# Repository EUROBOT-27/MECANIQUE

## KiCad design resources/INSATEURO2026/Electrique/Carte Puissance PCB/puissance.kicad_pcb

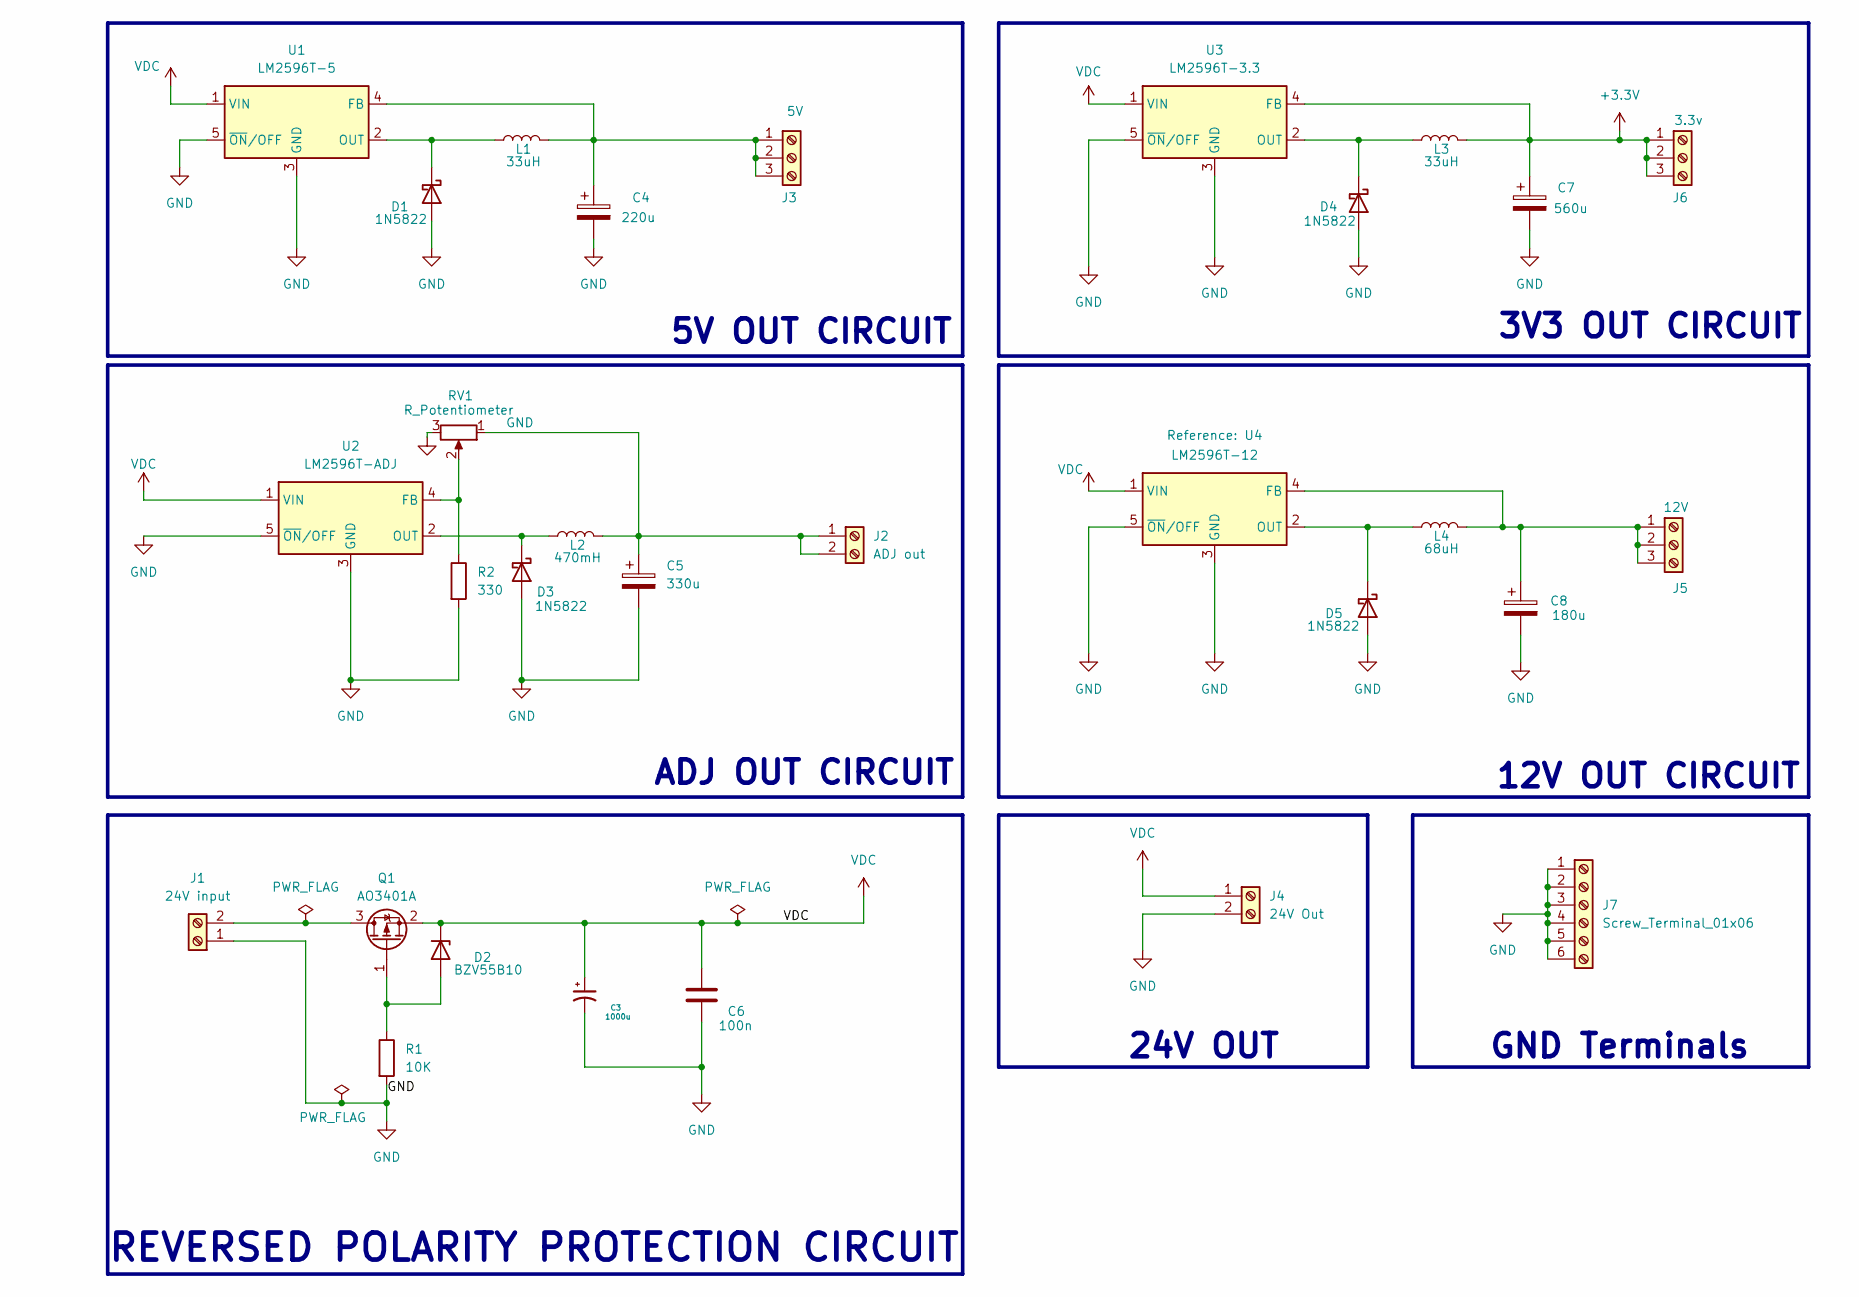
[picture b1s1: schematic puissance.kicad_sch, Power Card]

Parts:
C3: 1000u; CP_Elec_10x10.5
C4: 220u; CP_Elec_10x10.5
C5: 330u; CP_Elec_10x10.5
C6: 100n; C_1206_3216Metric_Pad1.33x1.80mm_HandSolder
C7: 560u; CP_Elec_10x10.5
C8: 180u; CP_Elec_10x10.5
D1, D3, D4, D5: 1N5822; D_DO-34_SOD68_P5.08mm_Vertical_AnodeUp
D2: BZV55B10; D_MiniMELF
J1: 24V input; Altech_AK100_1x02_P5.00mm
J2: ADJ out; Altech_AK100_1x02_P5.00mm
J3: 5V; Altech_AK100_1x03_P5.00mm
J4: 24V Out; Altech_AK100_1x02_P5.00mm
J5: 12V; Altech_AK100_1x03_P5.00mm
J6: 3.3v; Altech_AK100_1x03_P5.00mm
J7: Screw_Terminal_01x06; Altech_AK100_1x06_P5.00mm
L1, L3: 33uH; L_12x12mm_H6mm
L2: 470mH; L_12x12mm_H6mm
L4: 68uH; L_12x12mm_H6mm
Q1: AO3401A; SOT-23W
R1: 10K; R_1206_3216Metric_Pad1.30x1.75mm_HandSolder
R2: 330; R_1206_3216Metric_Pad1.30x1.75mm_HandSolder
RV1: R_Potentiometer; Potentiometer_Bourns_3296W_Vertical
U1: LM2596T-5; TO-263-5_TabPin3
U2: LM2596T-ADJ; TO-263-5_TabPin3
U3: LM2596T-3.3; TO-263-5_TabPin3
U4: LM2596T-12; TO-263-5_TabPin3

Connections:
+3.3V: C7.1, J6.1, J6.2, J6.3, L3.2, U3.4 (FB)
GND: C3.2, C4.2, C5.2, C6.2, C7.2, C8.2, D1.2 (A), D3.2 (A), D4.2 (A), D5.2 (A), J1.1, J4.2, J7.1, J7.2, J7.3, J7.4, J7.5, J7.6, R1.2, R2.2, RV1.3, U1.3 (GND), U1.5 (~ON/OFF), U2.3 (GND), U2.5 (~ON/OFF), U3.3 (GND), U3.5 (~ON/OFF), U4.3 (GND), U4.5 (~ON/OFF)
unnamed: D1.1 (K), L1.1, U1.2 (OUT)
unnamed: D2.2 (A), Q1.1 (G), R1.1
unnamed: D3.1 (K), L2.1, U2.2 (OUT)
unnamed: D4.1 (K), L3.1, U3.2 (OUT)
unnamed: D5.1 (K), L4.1, U4.2 (OUT)
unnamed: J1.2, Q1.3 (D)
unnamed: C5.1, J2.1, J2.2, L2.2, RV1.1
unnamed: C4.1, J3.1, J3.2, J3.3, L1.2, U1.4 (FB)
unnamed: C8.1, J5.1, J5.2, J5.3, L4.2, U4.4 (FB)
unnamed: R2.1, RV1.2, U2.4 (FB)
VDC: C3.1, C6.1, D2.1 (K), J4.1, Q1.2 (S), U1.1 (VIN), U2.1 (VIN), U3.1 (VIN), U4.1 (VIN)

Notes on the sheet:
5V OUT CIRCUIT
ADJ OUT CIRCUIT
12V OUT CIRCUIT
3V3 OUT CIRCUIT
REVERSED POLARITY PROTECTION CIRCUIT
24V OUT
GND Terminals

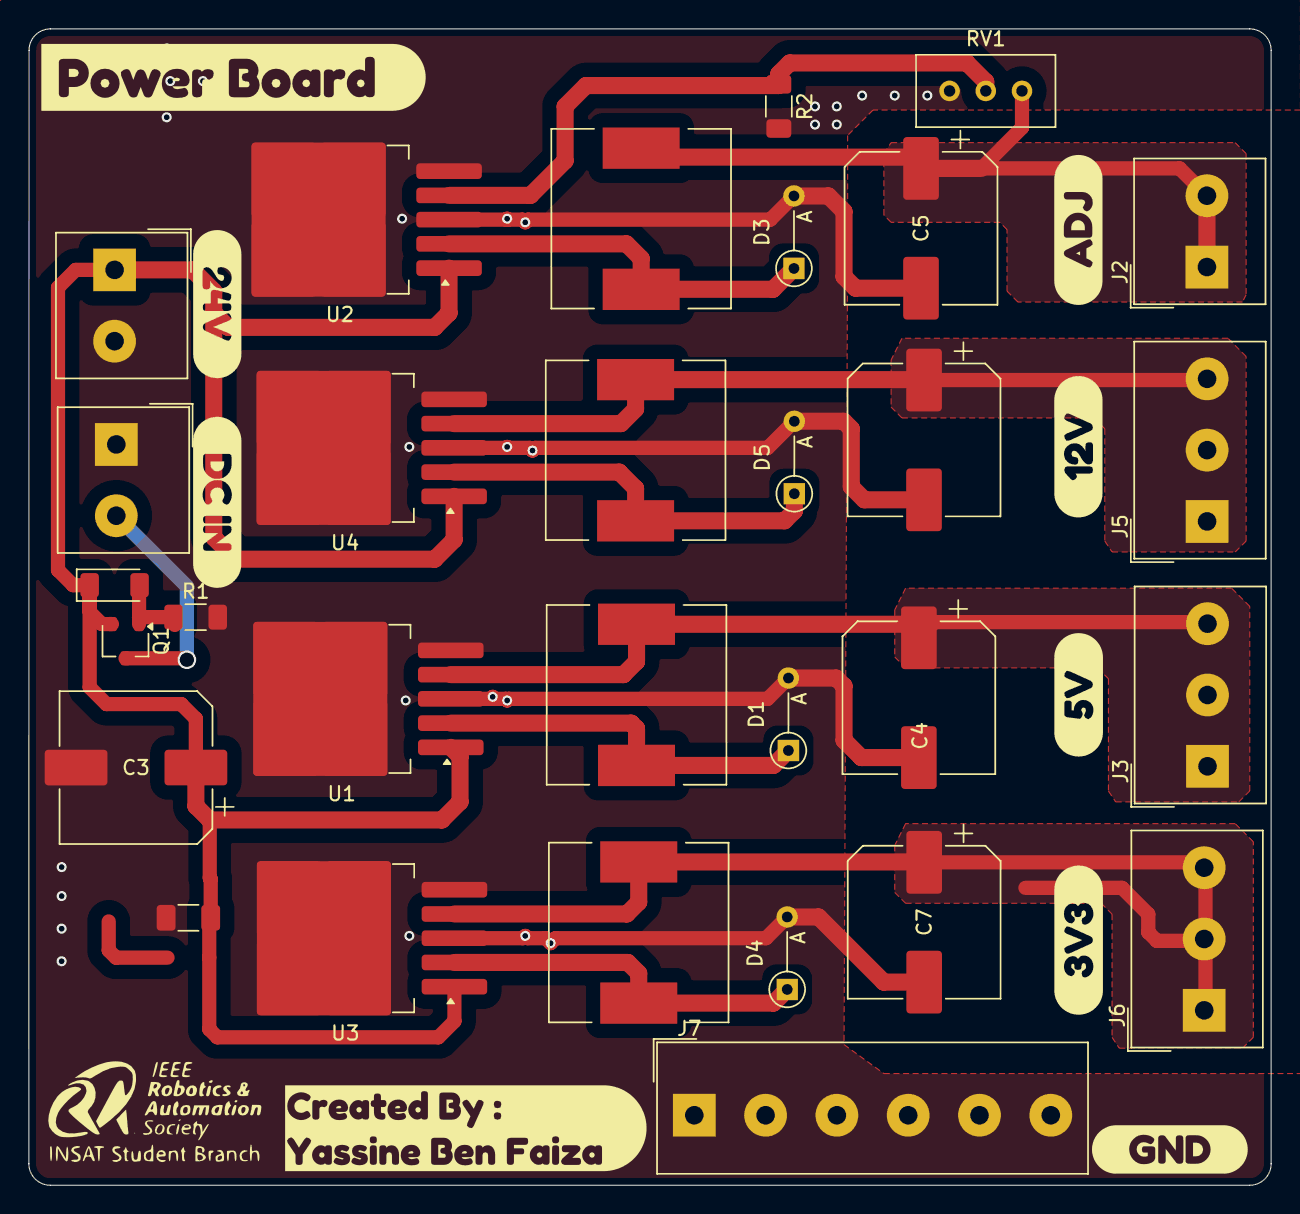
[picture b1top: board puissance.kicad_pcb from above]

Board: 2 copper layers, 87.1 x 81.1 mm, 39 parts (0 on the bottom side), 13 nets.

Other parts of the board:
kibuzzard-68827F3E: G***; kibuzzard-68827F3E
kibuzzard-679253A4: G***; kibuzzard-679253A4
kibuzzard-679255E3: G***; kibuzzard-679255E3
kibuzzard-688280F0: G***; kibuzzard-688280F0
kibuzzard-6792564A: G***; kibuzzard-6792564A
kibuzzard-67925436: G***; kibuzzard-67925436
kibuzzard-67925609: G***; kibuzzard-67925609
kibuzzard-67925625: G***; kibuzzard-67925625
kibuzzard-67925638: G***; kibuzzard-67925638

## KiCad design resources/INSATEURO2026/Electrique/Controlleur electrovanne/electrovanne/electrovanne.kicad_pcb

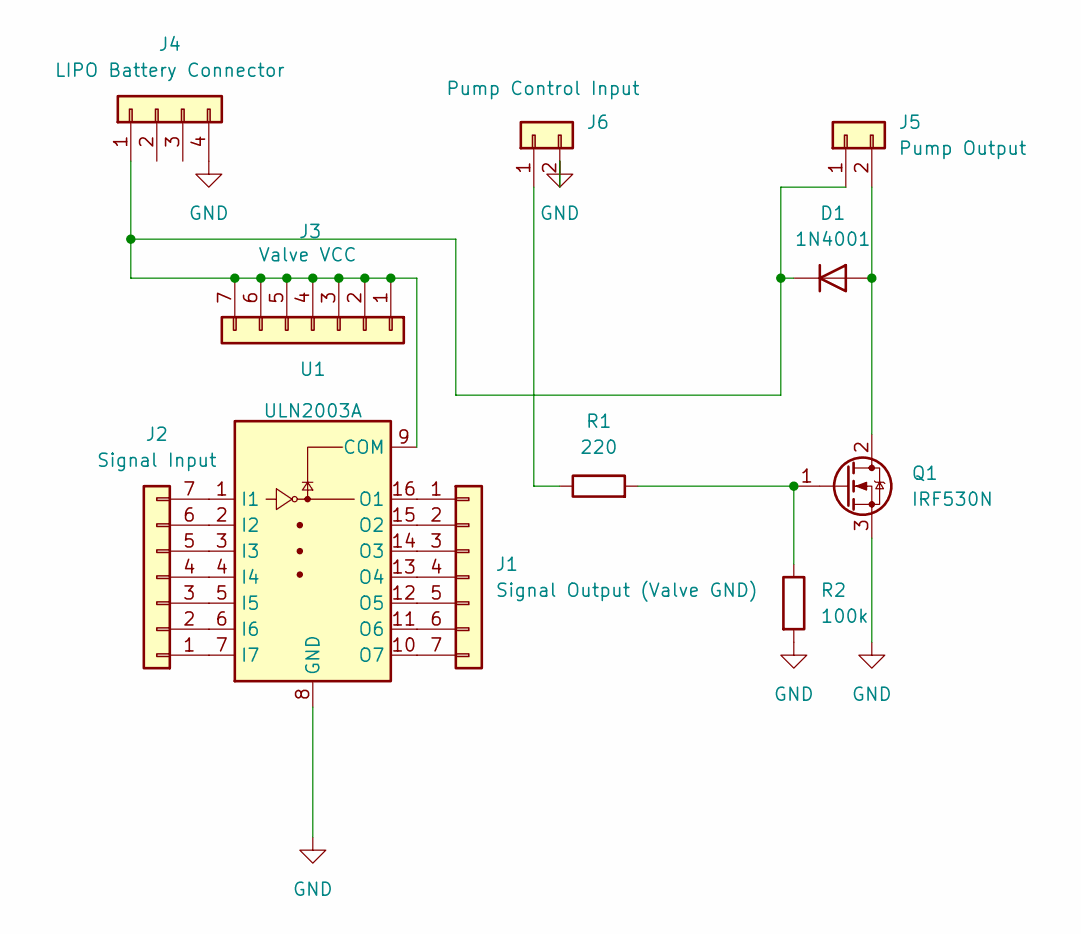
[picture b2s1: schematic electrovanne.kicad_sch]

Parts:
D1: 1N4001; D_DO-41_SOD81_P7.62mm_Horizontal
J1: Signal Output (Valve GND); PinSocket_1x08_P2.00mm_Vertical
J2: Signal Input; PinSocket_1x08_P2.00mm_Vertical
J3: Valve VCC; PinSocket_1x08_P2.00mm_Vertical
J4: LIPO Battery Connector; JST_XH_B4B-XH-A_1x04_P2.50mm_Vertical
J5: Pump Output; JST_EH_B2B-EH-A_1x02_P2.50mm_Vertical
J6: Pump Control Input; PinHeader_1x02_P1.00mm_Vertical
Q1: IRF530N; TO-220-3_Vertical
R1: 220; R_Axial_DIN0207_L6.3mm_D2.5mm_P15.24mm_Horizontal
R2: 100k; R_Axial_DIN0207_L6.3mm_D2.5mm_P15.24mm_Horizontal
U1: ULN2003A; DIP-16_W7.62mm

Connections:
GND: J4.4, J6.2, Q1.3 (S), R2.2, U1.8 (GND)
unnamed: D1.2 (A), J5.2, Q1.2 (D)
unnamed: D1.1 (K), J3.1, J3.2, J3.3, J3.4, J3.5, J3.6, J3.7, J4.1, J5.1, U1.9 (COM)
unnamed: J1.1, U1.16 (O1)
unnamed: J1.2, U1.15 (O2)
unnamed: J1.3, U1.14 (O3)
unnamed: J1.4, U1.13 (O4)
unnamed: J1.5, U1.12 (O5)
unnamed: J1.6, U1.11 (O6)
unnamed: J1.7, U1.10 (O7)
unnamed: J2.1, U1.7 (I7)
unnamed: J2.2, U1.6 (I6)
unnamed: J2.3, U1.5 (I5)
unnamed: J2.4, U1.4 (I4)
unnamed: J2.5, U1.3 (I3)
unnamed: J2.6, U1.2 (I2)
unnamed: J2.7, U1.1 (I1)
unnamed: J6.1, R1.1
unnamed: Q1.1 (G), R1.2, R2.1

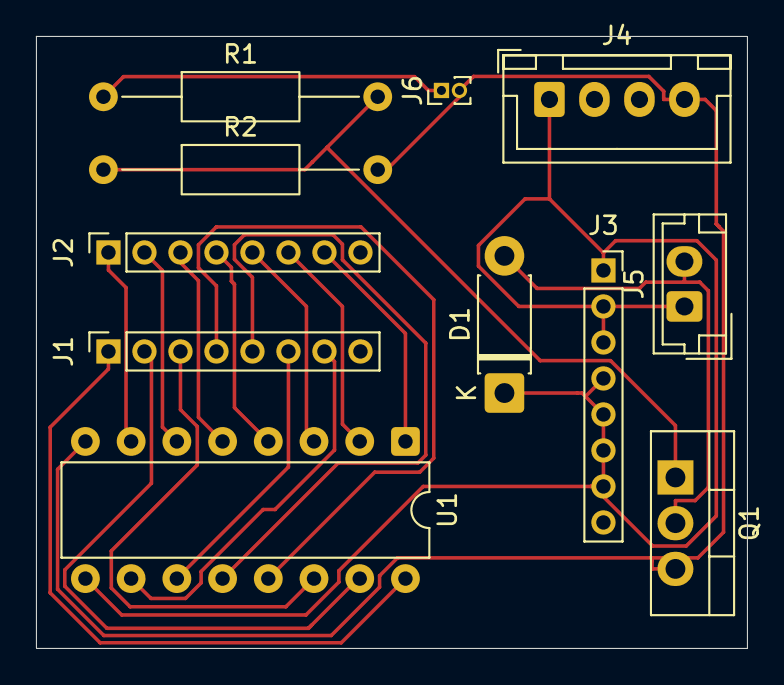
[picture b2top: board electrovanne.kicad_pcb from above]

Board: 2 copper layers, 39.5 x 34.0 mm, 11 parts (0 on the bottom side), 19 nets.

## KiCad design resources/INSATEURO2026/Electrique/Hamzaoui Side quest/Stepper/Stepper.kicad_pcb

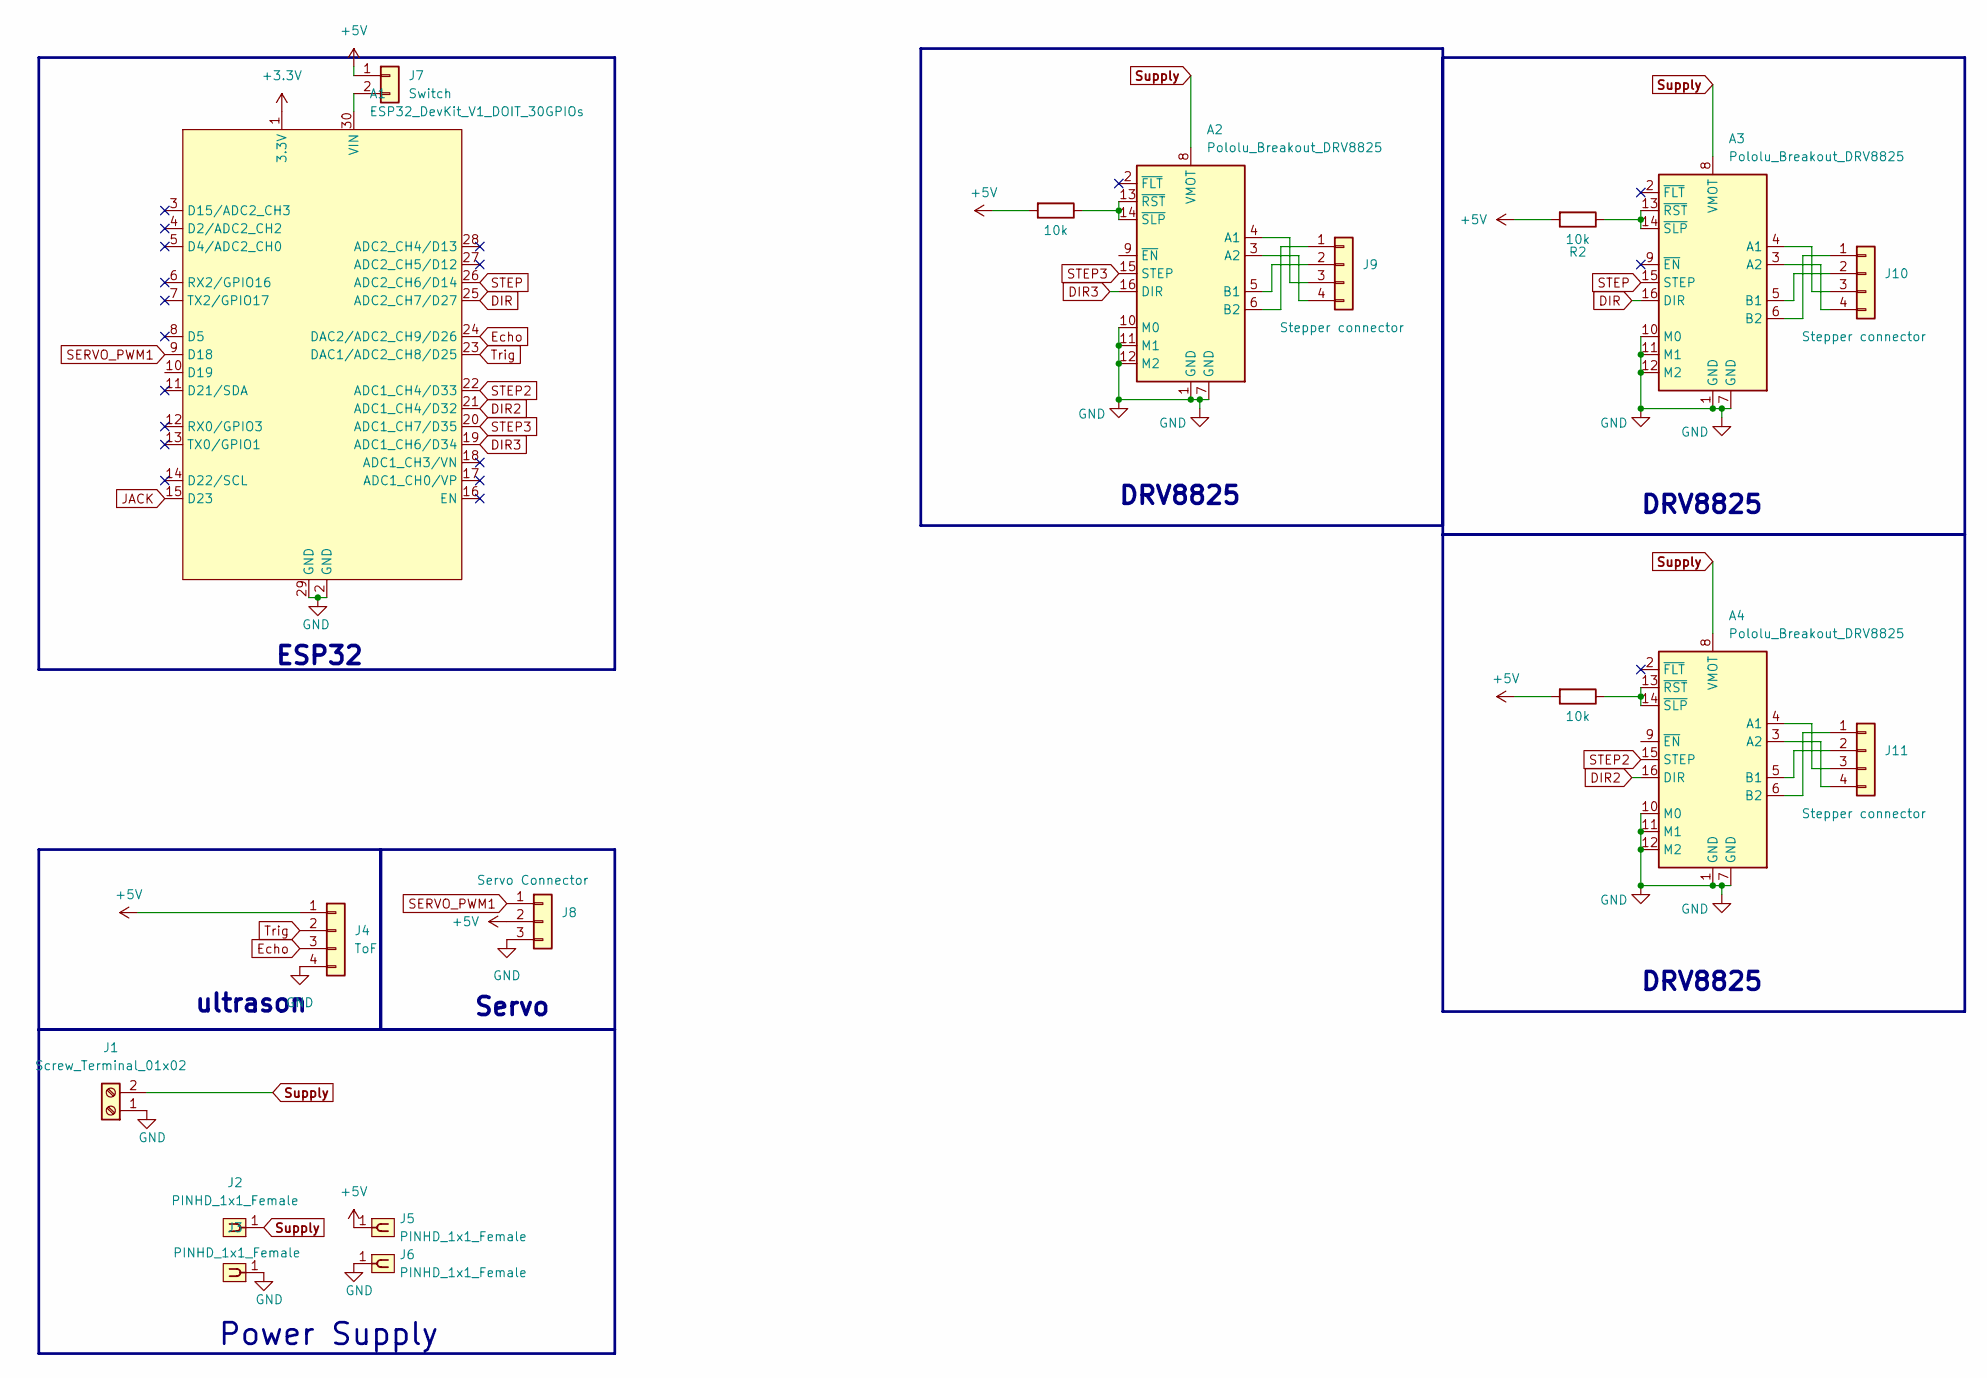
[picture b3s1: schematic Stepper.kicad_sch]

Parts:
A1: ESP32_DevKit_V1_DOIT_30GPIOs; DOIT_ESP32_DEVKIT_30Pins
A2, A3, A4: Pololu_Breakout_DRV8825; Pololu_Breakout-16_15.2x20.3mm
J1: Screw_Terminal_01x02; TerminalBlock_Altech_AK300-2_P5.00mm
J2, J3, J5, J6: PINHD_1x1_Female; PinSocket_1x01_P2.54mm_Vertical
J4: ToF; JST_EH_B4B-EH-A_1x04_P2.50mm_Vertical
J7: Switch; JST_PH_B2B-PH-K_1x02_P2.00mm_Vertical
J8: Servo Connector; PinHeader_1x03_P2.54mm_Vertical; Part Number 1-0301FBV0T
J9, J10, J11: Stepper connector; JST_EH_B4B-EH-A_1x04_P2.50mm_Vertical
R1, R2, R3: 10k; R_Axial_DIN0204_L3.6mm_D1.6mm_P7.62mm_Horizontal

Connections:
+3.3V: A1.1 (3.3V)
+5V: J4.1, J5.1, J7.1, J8.2, R1.2, R2.2, R3.2
DIR: A1.25 (ADC2_CH7/D27), A3.16 (DIR)
DIR2: A1.21 (ADC1_CH4/D32), A4.16 (DIR)
DIR3: A1.19 (ADC1_CH6/D34), A2.16 (DIR)
Echo: A1.24 (DAC2/ADC2_CH9/D26), J4.3
GND: A1.2 (GND), A1.29 (GND), A2.1 (GND), A2.7 (GND), A2.10 (M0), A2.11 (M1), A2.12 (M2), A3.1 (GND), A3.7 (GND), A3.10 (M0), A3.11 (M1), A3.12 (M2), A4.1 (GND), A4.7 (GND), A4.10 (M0), A4.11 (M1), A4.12 (M2), J1.1, J3.1, J4.4, J6.1, J8.3
JACK: A1.15 (D23)
unnamed: A1.30 (VIN), J7.2
unnamed: A2.4 (A1), J9.3
unnamed: A2.3 (A2), J9.4
unnamed: A2.5 (B1), J9.2
unnamed: A2.6 (B2), J9.1
unnamed: A2.13 (~RST), A2.14 (~SLP), R1.1
unnamed: A3.4 (A1), J10.3
unnamed: A3.3 (A2), J10.4
unnamed: A3.5 (B1), J10.2
unnamed: A3.6 (B2), J10.1
unnamed: A3.13 (~RST), A3.14 (~SLP), R2.1
unnamed: A4.4 (A1), J11.3
unnamed: A4.3 (A2), J11.4
unnamed: A4.5 (B1), J11.2
unnamed: A4.6 (B2), J11.1
unnamed: A4.13 (~RST), A4.14 (~SLP), R3.1
SERVO_PWM1: A1.9 (D18), J8.1
STEP: A1.26 (ADC2_CH6/D14), A3.15 (STEP)
STEP2: A1.22 (ADC1_CH4/D33), A4.15 (STEP)
STEP3: A1.20 (ADC1_CH7/D35), A2.15 (STEP)
Supply: A2.8 (VMOT), A3.8 (VMOT), A4.8 (VMOT), J1.2, J2.1
Trig: A1.23 (DAC1/ADC2_CH8/D25), J4.2

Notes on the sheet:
ultrason
Power Supply
ESP32
DRV8825
Servo

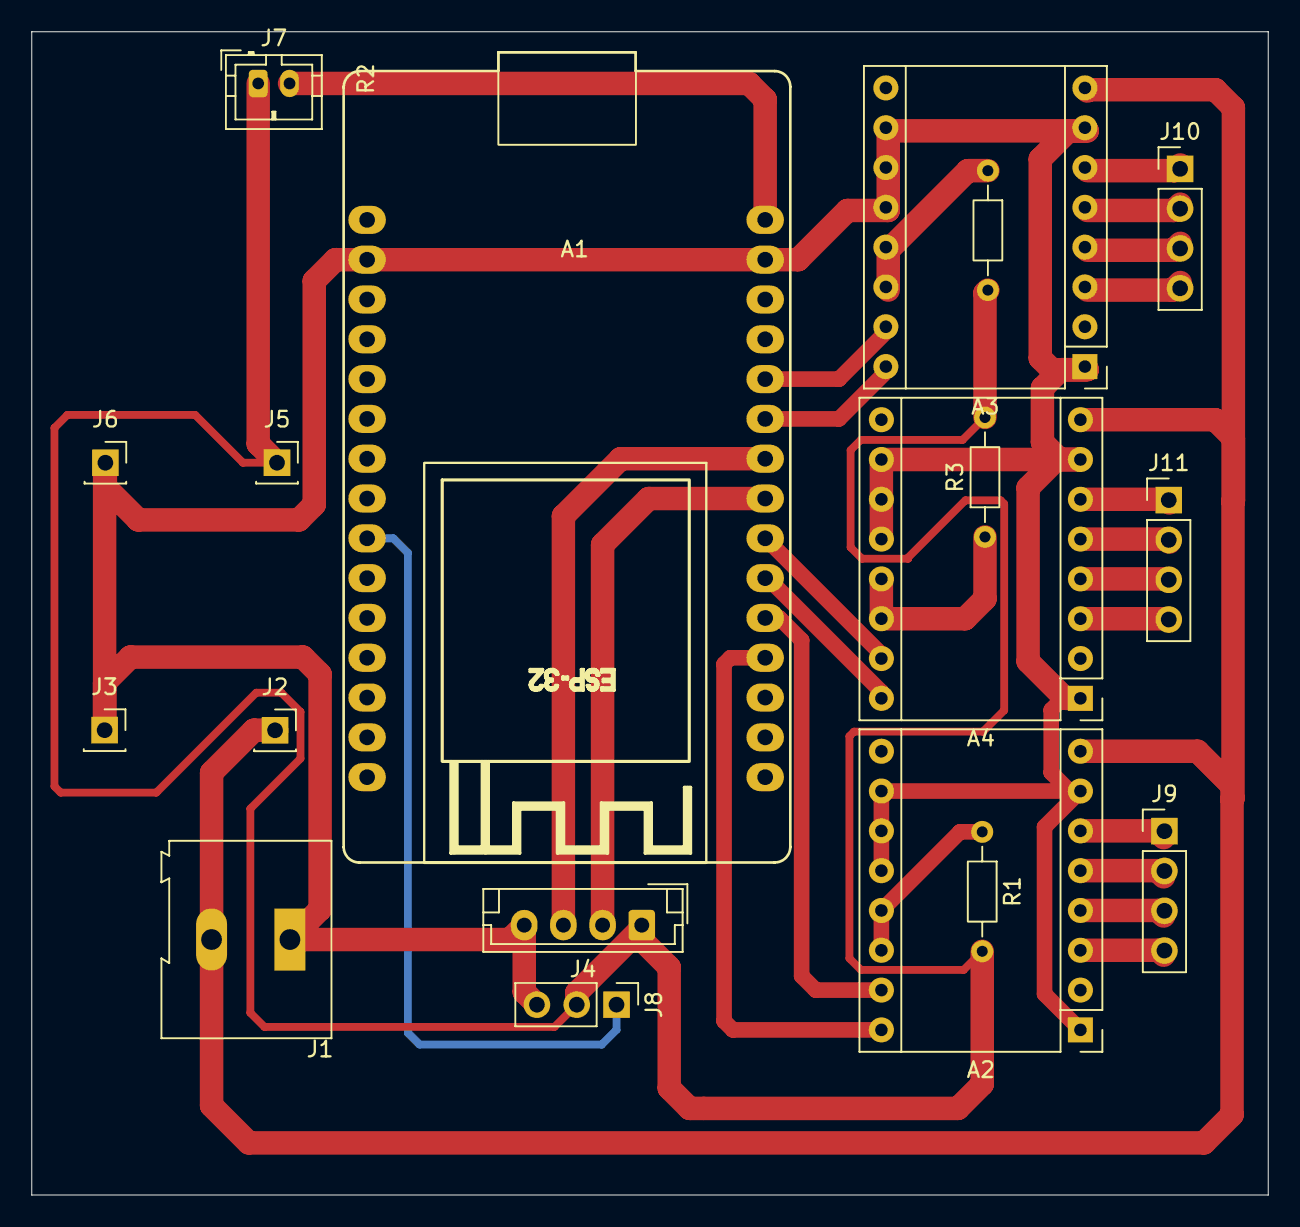
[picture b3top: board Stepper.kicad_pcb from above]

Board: 2 copper layers, 78.9 x 74.2 mm, 18 parts (0 on the bottom side), 28 nets.

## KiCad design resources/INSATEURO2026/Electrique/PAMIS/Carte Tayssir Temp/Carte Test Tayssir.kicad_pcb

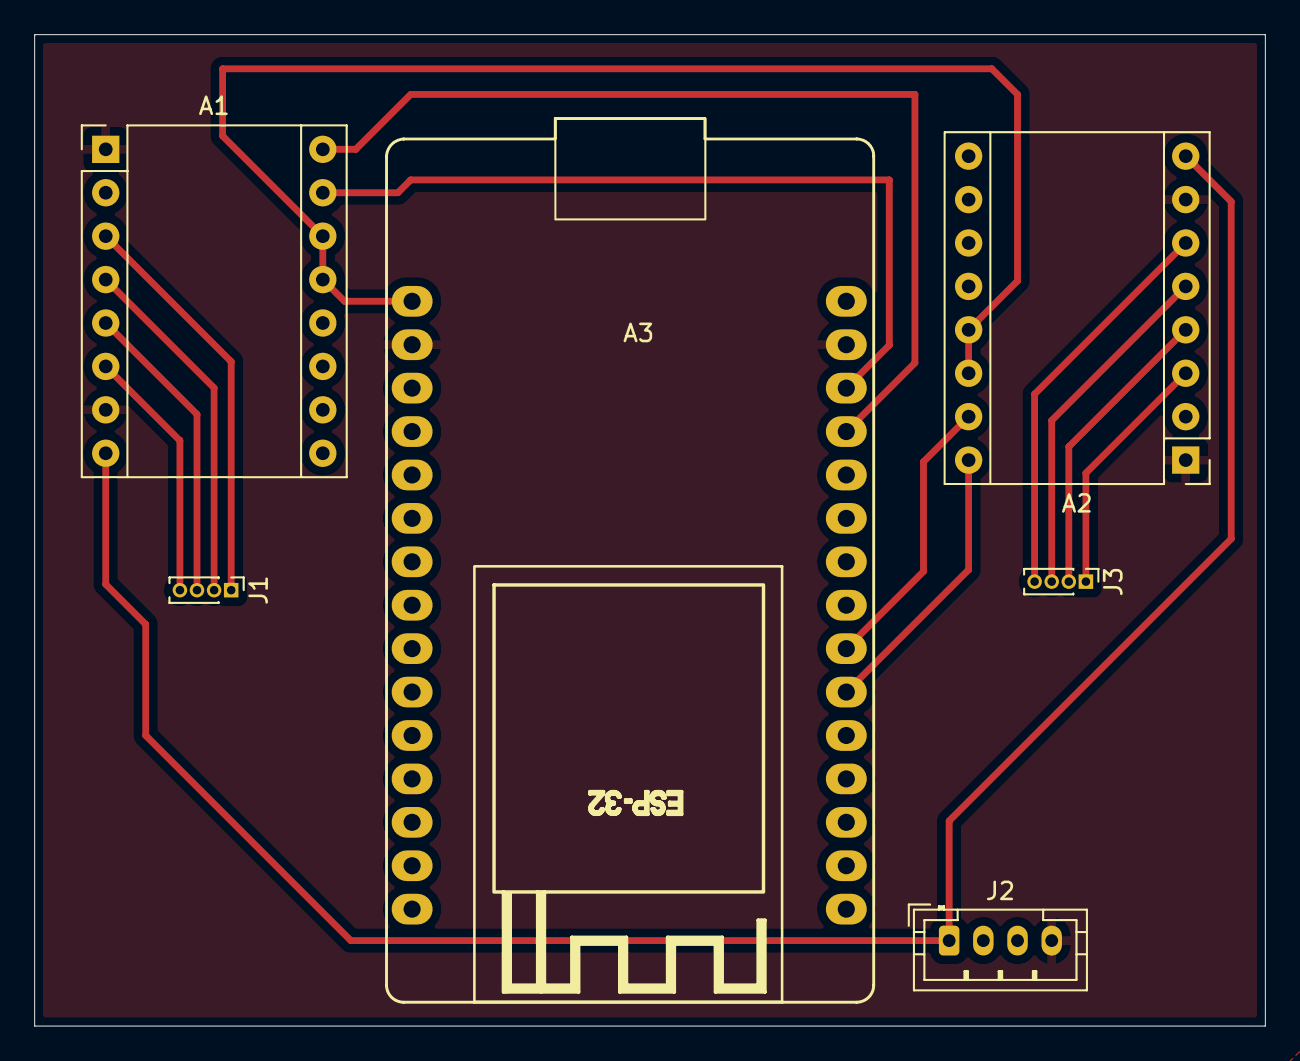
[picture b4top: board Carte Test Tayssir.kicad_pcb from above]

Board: 2 copper layers, 72.0 x 58.0 mm, 6 parts (0 on the bottom side), 15 nets.

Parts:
A1, A2: Pololu_Breakout_DRV8825; Pololu_Breakout-16_15.2x20.3mm
A3: ESP32_DevKit_V1_DOIT_30GPIOs; DOIT_ESP32_DEVKIT_30Pins
J1, J3: Conn_01x04_Pin; PinHeader_1x04_P1.00mm_Vertical
J2: Conn_01x04; JST_PH_B4B-PH-K_1x04_P2.00mm_Vertical

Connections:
3V3: A1.13 (~RST), A1.14 (~SLP), A2.13 (~RST), A2.14 (~SLP), A3.1 (3.3V)
12V: A1.8 (VMOT), A2.8 (VMOT), J2.1
GND: A1.1 (GND), A1.7 (GND), A2.1 (GND), A2.7 (GND), A3.2 (GND), A3.29 (GND), J2.4
unnamed: A1.4 (A1), J1.2
unnamed: A1.3 (A2), J1.1
unnamed: A1.5 (B1), J1.3
unnamed: A1.6 (B2), J1.4
unnamed: A1.16 (DIR), A3.27 (ADC2_CH5/D12)
unnamed: A1.15 (STEP), A3.28 (ADC2_CH4/D13)
unnamed: A2.4 (A1), J3.2
unnamed: A2.3 (A2), J3.1
unnamed: A2.5 (B1), J3.3
unnamed: A2.6 (B2), J3.4
unnamed: A2.16 (DIR), A3.21 (ADC1_CH4/D32)
unnamed: A2.15 (STEP), A3.22 (ADC1_CH4/D32)

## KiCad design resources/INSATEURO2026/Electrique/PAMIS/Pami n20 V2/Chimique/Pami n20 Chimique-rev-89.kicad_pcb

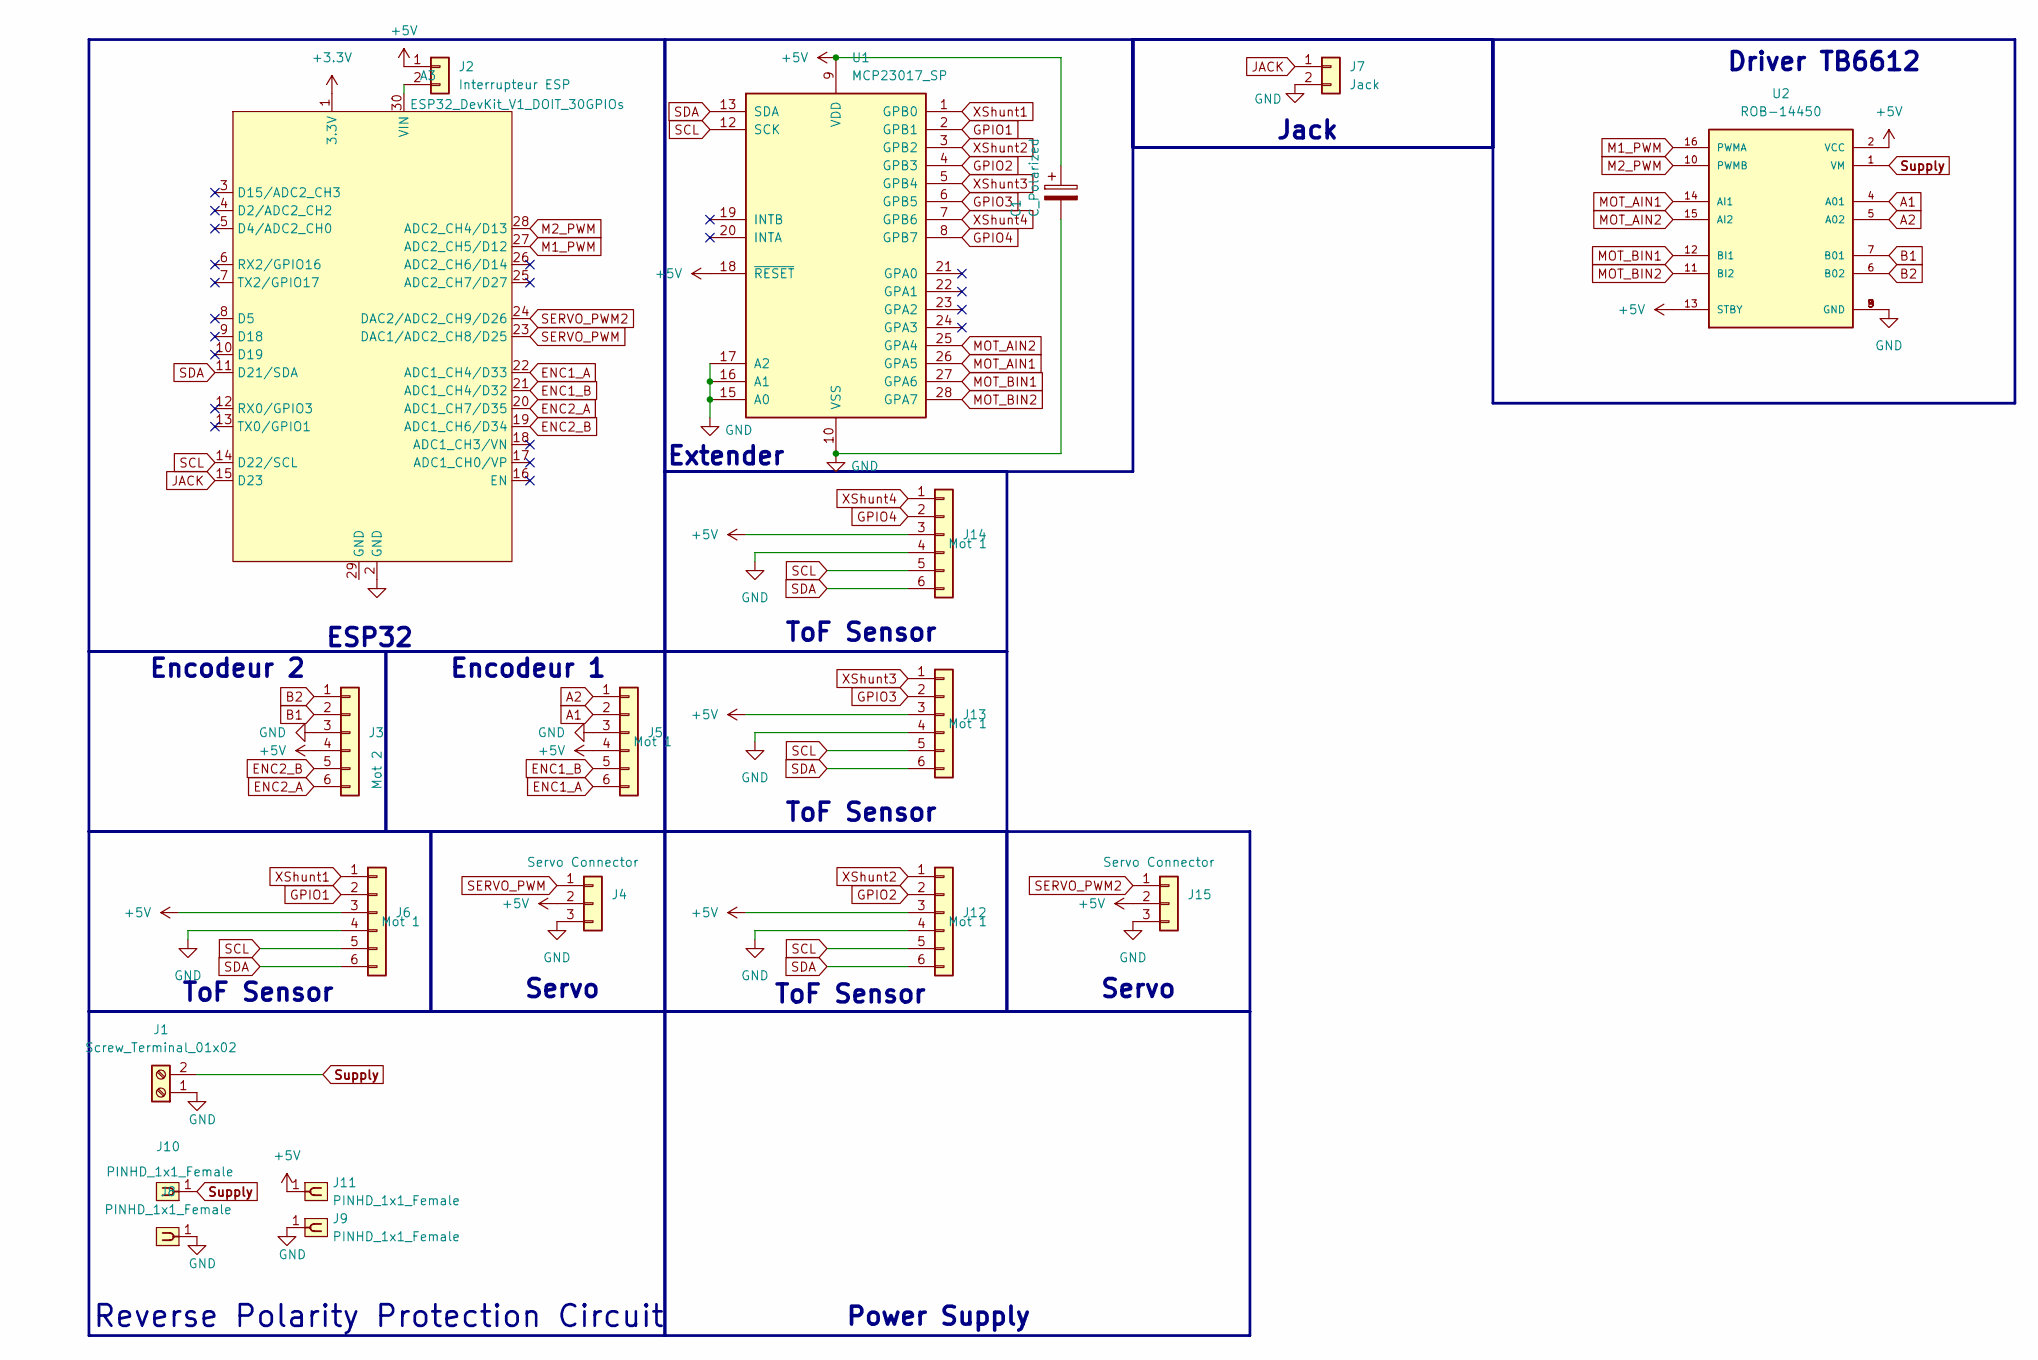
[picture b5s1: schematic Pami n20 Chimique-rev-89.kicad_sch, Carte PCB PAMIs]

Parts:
A3: ESP32_DevKit_V1_DOIT_30GPIOs; DOIT_ESP32_DEVKIT_30Pins
C1: C_Polarized; CP_Axial_L10.0mm_D4.5mm_P15.00mm_Horizontal
J1: Screw_Terminal_01x02; ScrewTerminal_1x02_P3.5mm_Blue
J2: Interrupteur ESP; JST_PH_B2B-PH-K_1x02_P2.00mm_Vertical
J3: Mot 2; JST_EH_B6B-EH-A_1x06_P2.50mm_Vertical; Part Number 1-0601FBV0T
J4, J15: Servo Connector; PinHeader_1x03_P2.54mm_Vertical; Part Number 1-0301FBV0T
J5, J6, J12, J13, J14: Mot 1; JST_EH_B6B-EH-A_1x06_P2.50mm_Vertical
J7: Jack; JST_EH_B6B-EH-A_1x06_P2.50mm_Vertical
J8, J9, J10, J11: PINHD_1x1_Female; PinSocket_1x01_P2.54mm_Vertical
U1: MCP23017_SP; DIP-28_W7.62mm_Socket
U2: ROB-14450; MODULE_ROB-14450; PARTREV 11-13-17

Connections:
+3.3V: A3.1 (3.3V)
+5V: A3.30 (VIN), C1.1, J2.1, J2.2, J3.4, J4.2, J5.4, J6.3, J11.1, J12.3, J13.3, J14.3, J15.2, U1.9 (VDD), U1.18 (~RESET), U2.2 (VCC), U2.13 (STBY)
A1: J5.2, U2.4 (A01)
A2: J5.1, U2.5 (A02)
B1: J3.2, U2.7 (B01)
B2: J3.1, U2.6 (B02)
ENC1_A: A3.22 (ADC1_CH4/D33), J5.6
ENC1_B: A3.21 (ADC1_CH4/D32), J5.5
ENC2_A: A3.20 (ADC1_CH7/D35), J3.6
ENC2_B: A3.19 (ADC1_CH6/D34), J3.5
GND: A3.2 (GND), C1.2, J1.1, J3.3, J4.3, J5.3, J6.4, J7.2, J8.1, J9.1, J12.4, J13.4, J14.4, J15.3, U1.10 (VSS), U1.15 (A0), U1.16 (A1), U1.17 (A2), U2.3 (GND), U2.8 (GND), U2.9 (GND)
GPIO1: J6.2, U1.2 (GPB1)
GPIO2: J12.2, U1.4 (GPB3)
GPIO3: J13.2, U1.6 (GPB5)
GPIO4: J14.2, U1.8 (GPB7)
JACK: A3.15 (D23), J7.1
M1_PWM: A3.27 (ADC2_CH5/D12), U2.16 (PWMA)
M2_PWM: A3.28 (ADC2_CH4/D13), U2.10 (PWMB)
MOT_AIN1: U1.26 (GPA5), U2.14 (AI1)
MOT_AIN2: U1.25 (GPA4), U2.15 (AI2)
MOT_BIN1: U1.27 (GPA6), U2.12 (BI1)
MOT_BIN2: U1.28 (GPA7), U2.11 (BI2)
SCL: A3.14 (D22/SCL), J6.5, J12.5, J13.5, J14.5, U1.12 (SCK)
SDA: A3.11 (D21/SDA), J6.6, J12.6, J13.6, J14.6, U1.13 (SDA)
SERVO_PWM: A3.23 (DAC1/ADC2_CH8/D25), J4.1
SERVO_PWM2: A3.24 (DAC2/ADC2_CH9/D26), J15.1
Supply: J1.2, J10.1, U2.1 (VM)
XShunt1: J6.1, U1.1 (GPB0)
XShunt2: J12.1, U1.3 (GPB2)
XShunt3: J13.1, U1.5 (GPB4)
XShunt4: J14.1, U1.7 (GPB6)

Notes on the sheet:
Servo
ToF Sensor
Jack
ESP32
Power Supply
Extender
Reverse Polarity Protection Circuit
Driver TB6612
Encodeur 1
Encodeur 2

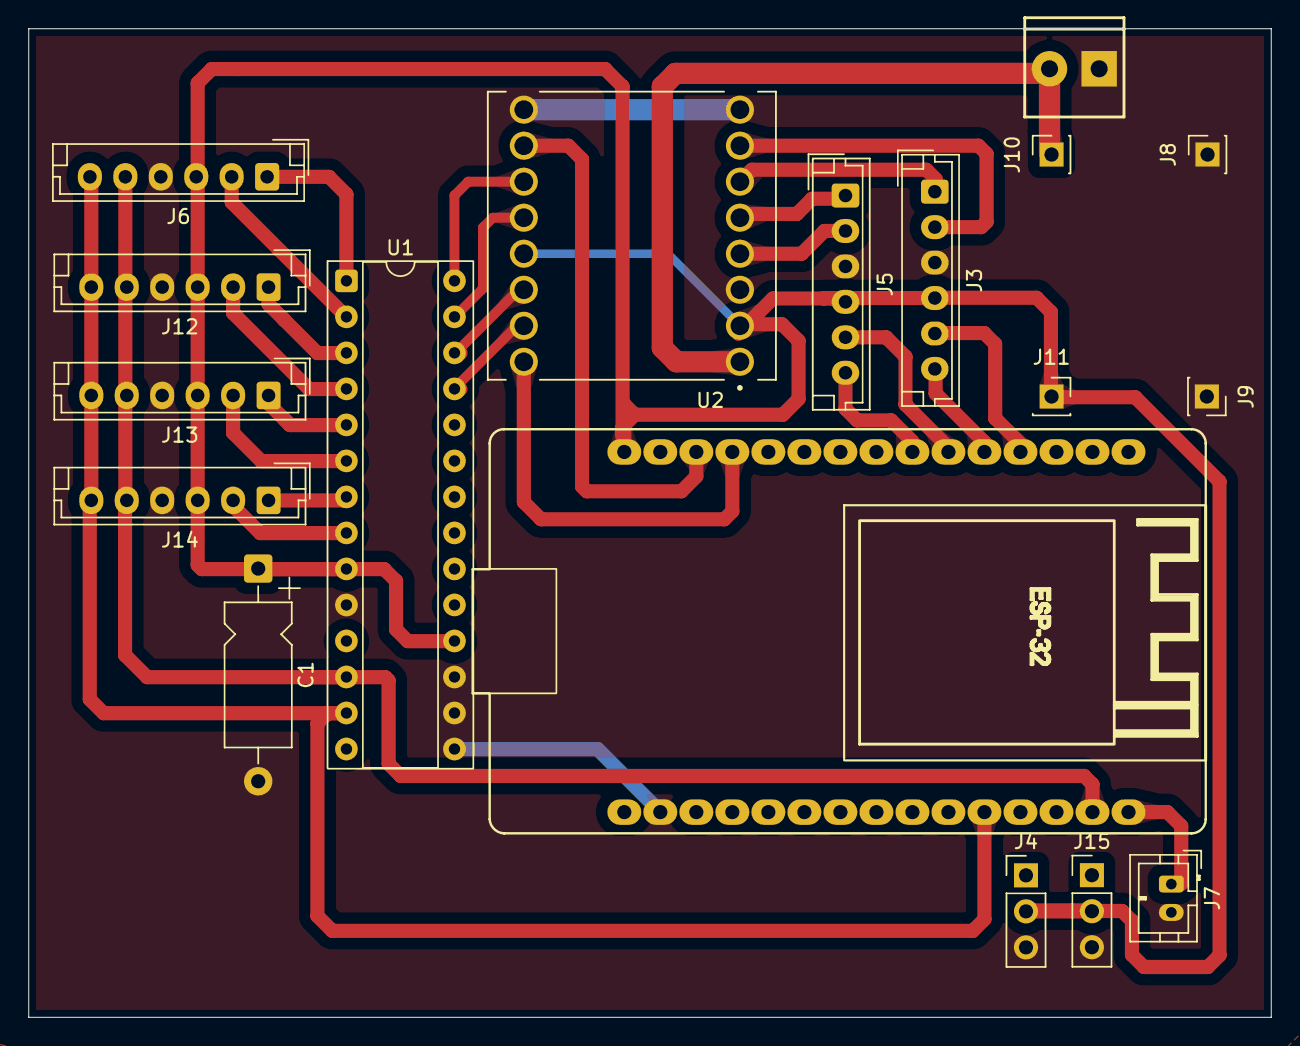
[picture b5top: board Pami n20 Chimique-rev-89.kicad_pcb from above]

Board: 2 copper layers, 87.6 x 69.7 mm, 18 parts (0 on the bottom side), 30 nets.

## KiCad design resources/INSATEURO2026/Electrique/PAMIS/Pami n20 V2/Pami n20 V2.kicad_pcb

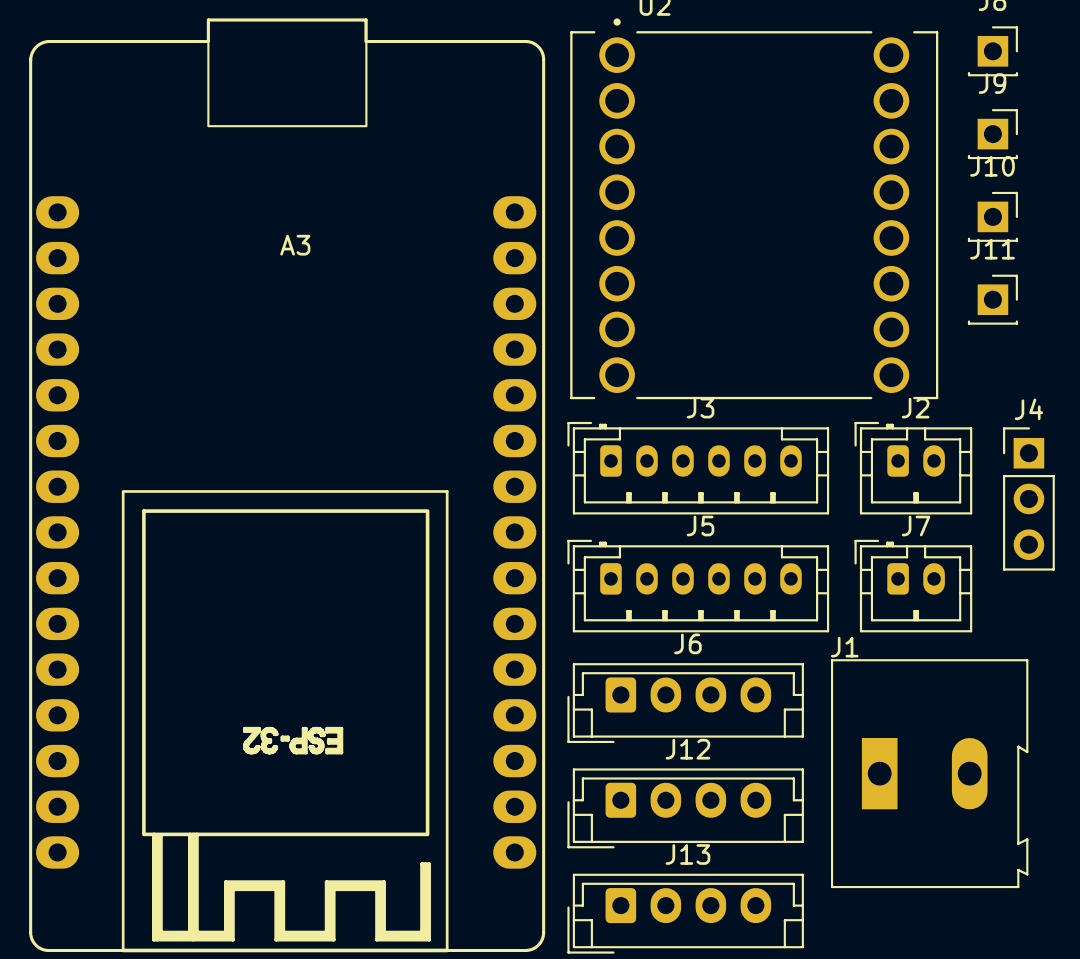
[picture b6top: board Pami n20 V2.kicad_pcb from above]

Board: 2 copper layers, 15 parts (0 on the bottom side), 23 nets, no tracks yet.

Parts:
A3: ESP32_DevKit_V1_DOIT_30GPIOs; DOIT_ESP32_DEVKIT_30Pins
J1: Screw_Terminal_01x02; TerminalBlock_Altech_AK300-2_P5.00mm
J2, J7: Jack; JST_PH_B2B-PH-K_1x02_P2.00mm_Vertical
J3: Mot 2; JST_PH_B6B-PH-K_1x06_P2.00mm_Vertical
J4: Servo Connector; PinHeader_1x03_P2.54mm_Vertical
J5: Mot 1; JST_PH_B6B-PH-K_1x06_P2.00mm_Vertical
J6, J12, J13: ToF; JST_EH_B4B-EH-A_1x04_P2.50mm_Vertical
J8, J9, J10, J11: PINHD_1x1_Female; PinSocket_1x01_P2.54mm_Vertical
U2: ROB-14450; MODULE_ROB-14450

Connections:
+3.3V: A3.1 (3.3V), J6.1, J12.1, J13.1, U2.2 (VCC)
+5V: A3.30 (VIN), J3.2, J4.2, J5.2, J9.1, U2.1 (VM), U2.13 (STBY)
A1: J5.1, U2.4 (A01)
A2: J5.6, U2.5 (A02)
B1: J3.1, U2.7 (B01)
B2: J3.6, U2.6 (B02)
ENC1_A: A3.22 (ADC1_CH4/D33), J5.4
ENC1_B: A3.21 (ADC1_CH4/D32), J5.3
ENC2_A: A3.20 (ADC1_CH7/D35), J3.4
ENC2_B: A3.19 (ADC1_CH6/D34), J3.3
GND: A3.2 (GND), J1.1, J3.5, J4.3, J5.5, J6.2, J7.2, J10.1, J11.1, J12.2, J13.2, U2.3 (GND), U2.8 (GND), U2.9 (GND)
JACK: A3.3 (D15/ADC2_CH3), J7.1
M1_PWM: A3.18 (ADC1_CH3/VN), U2.16 (PWMA)
M2_PWM: A3.27 (ADC2_CH5/D12), U2.10 (PWMB)
MOT_AIN1: A3.24 (DAC2/ADC2_CH9/D26), U2.14 (AI1)
MOT_AIN2: A3.23 (DAC1/ADC2_CH8/D25), U2.15 (AI2)
MOT_BIN1: A3.25 (ADC2_CH7/D27), U2.12 (BI1)
MOT_BIN2: A3.26 (ADC2_CH6/D14), U2.11 (BI2)
unnamed: J1.2, J2.1
SCL: A3.14 (D22/SCL), J6.3, J12.3, J13.3
SDA: A3.11 (D21/SDA), J6.4, J12.4, J13.4
SERVO_PWM: A3.17 (ADC1_CH0/VP), J4.1
Supply: J2.2, J8.1
